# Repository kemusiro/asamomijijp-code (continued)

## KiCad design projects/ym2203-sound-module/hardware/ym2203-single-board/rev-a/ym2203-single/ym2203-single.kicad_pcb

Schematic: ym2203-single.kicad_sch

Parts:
A1: Raspberry Pi Pico 2; A1
A2: AE-PCM5102A / I2S 48kHz; A2
A3: AE-LLCNV-LVC8T245; A3
A4: AE-LLCNV-LVC8T245; A4
C1: 47u 10V; C1
C2: 10u 10V; C2
C3: 100n; C3
C4: 10u 10V; C4
C5: 100n; C5
C6: 100n; C6
C7: 100n; C7
C8: 100n; C8
C9: 100n; C9
C10: 100n; C10
C11: 100n; C11
C12: 100n; C12
C13: 2.2u X7R 10V; C13
C14: 2.2u X7R 10V; C14
C15: 1u X7R 10V; C15
C16: 100n; C16
C17: 100n; C17
C18: 100n; C18
C19: 10u 10V; C19
C20: 10u 10V; C20
C21: 10u 10V; C21
C22: 2.2n C0G; C22
C23: 100n; C23
C24: 10u 10V; C24
C25: 4.7u BP 10V; C25
C26: 4.7u BP 10V; C26
C27: 4.7u BP 10V; C27
C28: 4.7u BP 10V; C28
C29: 47p; C29
C30: 100n; C30
C31: 4.7u BP 10V; C31
D1: SS14 / A=+5V K=VSYS; D1
F1: PTC 0.5A hold; F1
H1: M3 / 3.2mm NPTH; H1
H2: M3 / 3.2mm NPTH; H2
H3: M3 / 3.2mm NPTH; H3
H4: M3 / 3.2mm NPTH; H4
JHOST: HOST 3.3V I2C; JHOST
JLINE: TRS JACK / AMS-22 LINE IN; JLINE
JPOWER: MAIN INPUT / REGULATED DC 5V; JPOWER
JRUN: RESET SWITCH; JRUN
JVOL: EXTERNAL SINGLE 10k A POT; JVOL
Q1: MMBT3904 / B1 E2 C3; Q1
R1: 4.7k; R1
R2: 4.7k; R2
R3: 4.7k; R3
R4: 10k; R4
R5: 10k; R5
R6: 10k; R6
R7: 47; R7
R8: 47; R8
R9: 47; R9
R10: 47; R10
R11: 47; R11
R12: 470; R12
R13: 10k 1%; R13
R14: 10k 1%; R14
R15: 100k 1%; R15
R16: 100k 1%; R16
R17: 100k 1%; R17
R18: 100k 1%; R18
R19: 22k 1%; R19
R20: 10k; R20
R21: 100k; R21
R22: 10k; R22
R23: 100k; R23
R24: 100; R24
R25: 100; R25
RN1: RKC8BD103J; RN1
RN2: RKC8BD103J; RN2
RN3: RKC4BD103J; RN3
RN4: RKC4BD103J; RN4
RN5: RKC8BD102J; RN5
RN6: RKC8BD103J; RN6
TP1: +5V; TP1
TP2: +3V3; TP2
TP3: GND; TP3
TP4: ARM; TP4
TP5: RESET_N; TP5
TP6: Y_SD; TP6
TP7: Y_CLK; TP7
TP8: Y_SH; TP8
TP9: CLK4; TP9
TP10: MIX_MONO; TP10
TP11: VREF; TP11
TP12: DAC_L; TP12
U1: YM2203C / DIP40; U1
U2: 74LCX245FT / 3.3V; U2
U3: 74LCX245FT / 3.3V; U3
U4: TC74HC04AP / 3.3V; U4
U5: TC74HC00AP / 3.3V; U5
U6: TC74HC32AP / 3.3V; U6
U7: TC74HC74AP / 5V; U7
U8: MCP6022-I/P / reference + mono mixer; U8
U9: CD74HC4053E / line mute; U9
U10: TC74HC08AP / 3.3V; U10
X1: 8MHz 5V oscillator; X1

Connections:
/+3V3: A1.36 (3V3 OUT), A2.1 (CPVDD), A2.8 (AVDD), A2.20 (DVDD), A3.1 (VA), A3.3 (DIR A>B), A3.24 (VA), A4.1 (VA), A4.3 (DIR A>B), A4.24 (VA), C2.1, C5.1, C6.1, C7.1, C8.1, C9.1, C10.1, C16.1, C17.1, C18.1, C19.1, C20.1, C21.1, R1.2, R2.2, R4.2, R5.2, RN3.1 (COM), TP2.1, U2.1 (DIR A>B), U2.20 (VCC), U3.1 (DIR A>B), U3.20 (VCC), U4.14 (VCC), U5.14 (VCC), U6.14 (VCC), U10.14 (VCC)
/+5V: A3.23 (VB), A4.23 (VB), C1.1, C3.1, C4.1, C11.1, C12.1, C23.1, C30.1, D1.2 (A), F1.2, R13.1, R22.1, RN4.1 (COM), TP1.1, U1.21 (VDD), U7.1 (CLR1_N), U7.4 (PRE1_N), U7.10 (PRE2_N), U7.13 (CLR2_N), U7.14 (VCC), U8.8 (VDD), U9.16 (VCC), X1.8 (VCC)
/A0: A1.11 (GP8 / A0), A4.4 (A1), RN2.3 (R2)
/ARM: A1.29 (GP22 / ARM), RN2.2 (R1), TP4.1, U4.1 (1A), U5.1 (1A), U5.4 (2A), U10.1 (1A), U10.4 (2A), U10.9 (3A)
/CAPM: A2.4 (CAPM), C13.2
/CAPP: A2.2 (CAPP), C13.1
/CLK4: R8.2, TP9.1, U1.38 (PHI_M 4MHz)
/CLK8: R7.2, U7.3 (CLK1)
/CLK_FB: U7.2 (D1), U7.6 (Q1_N)
/CS_N: A1.17 (GP13 / CS_N), RN3.2 (R1), U6.1 (CS_N)
/D0: A1.1 (GP0 / D0), A3.4 (A1), RN1.2 (R1), U2.18 (B1)
/D1: A1.2 (GP1 / D1), A3.5 (A2), RN1.3 (R2), U2.17 (B2)
/D2: A1.4 (GP2 / D2), A3.6 (A3), RN1.4 (R3), U2.16 (B3)
/D3: A1.5 (GP3 / D3), A3.7 (A4), RN1.5 (R4), U2.15 (B4)
/D4: A1.6 (GP4 / D4), A3.8 (A5), RN1.6 (R5), U2.14 (B5)
/D5: A1.7 (GP5 / D5), A3.9 (A6), RN1.7 (R6), U2.13 (B6)
/D6: A1.9 (GP6 / D6), A3.10 (A7), RN1.8 (R7), U2.12 (B7)
/D7: A1.10 (GP7 / D7), A3.11 (A8), RN1.9 (R8), U2.11 (B8)
/DAC_ALLOW: A1.31 (GP26 / DAC_ALLOW), RN2.5 (R4), U10.5 (2B)
/DAC_BCK: A2.13 (BCK), R10.2
/DAC_DIN: A2.14 (DIN), R9.2
/DAC_L: A2.6 (OUTL), R12.1, TP12.1
/DAC_LRCK: A2.15 (LRCK), R11.2
/DAC_XSMT: A2.17 (XSMT), R6.1, U10.6 (2Y)
/DIV4: R8.1, U7.5 (Q1)
/EXT_5V: F1.1, JPOWER.1 (EXT_5V)
/FM_CLK: A1.22 (GP17 / FM_CLK), RN2.8 (R7), U3.17 (B2)
/FM_FILTER: C22.1, C28.1, R12.2
/FM_FILTER_AC: C28.2, R18.1
/FM_SD: A1.21 (GP16 / FM_SD), RN2.7 (R6), U3.18 (B1)
/FM_SH: A1.24 (GP18 / FM_SH), RN2.9 (R8), U3.16 (B3)
/GND: A1.3 (GND), A1.8 (GND), A1.13 (GND), A1.18 (GND), A1.23 (GND), A1.28 (GND), A1.33 (GND), A1.38 (GND), A2.3 (CPGND), A2.9 (AGND), A2.10 (DEMP), A2.11 (FLT), A2.12 (SCK), A2.16 (FMT), A2.19 (DGND), A3.12 (GND), A3.13 (GND), A3.22 (GND), A4.2 (OE_N), A4.9 (A6), A4.10 (A7), A4.11 (A8), A4.12 (GND), A4.13 (GND), A4.22 (GND), C1.2, C2.2, C3.2, C4.2, C5.2, C6.2, C7.2, C8.2, C9.2, C10.2, C11.2, C12.2, C14.2, C15.2, C16.2, C17.2, C18.2, C19.2, C20.2, C21.2, C22.2, C23.2, C24.2, C30.2, JHOST.1 (GND), JHOST.4 (GND), JLINE.3 (GND), JPOWER.2 (GND), JRUN.2 (GND), JVOL.3 (GND), Q1.2 (E), R3.2, R6.2, R14.2, R21.2, R23.2, RN1.1 (COM), RN2.1 (COM), RN5.1 (COM), RN6.1 (COM), TP3.1, U1.1 (GND), U1.17 (GND), U2.10 (GND), U3.6 (A5), U3.7 (A6), U3.8 (A7), U3.9 (A8), U3.10 (GND), U3.19 (OE_N), U4.5 (3A), U4.7 (GND), U4.9 (4A), U4.11 (5A), U4.13 (6A), U5.7 (GND), U5.9 (3A), U5.10 (3B), U5.12 (4A), U5.13 (4B), U6.7 (GND), U6.12 (4A), U6.13 (4B), U7.7 (GND), U7.11 (CLK2), U7.12 (D2), U8.4 (VSS), U9.1 (Y1), U9.2 (Y0), U9.3 (Z1), U9.5 (Z0), U9.6 (INH), U9.7 (VEE), U9.8 (GND), U9.9 (C), U9.10 (B), U10.7 (GND), U10.12 (4A), U10.13 (4B), X1.4 (GND)
/HOST_SCL: A1.27 (GP21 / HOST_SCL), JHOST.3 (HOST_SCL), R2.1
/HOST_SDA: A1.26 (GP20 / HOST_SDA), JHOST.2 (HOST_SDA), R1.1
/I2S_BCLK: A1.15 (GP11 / I2S_BCLK), R10.1
/I2S_DATA: A1.14 (GP10 / I2S_DATA), R9.1
/I2S_LRCK: A1.16 (GP12 / I2S_LRCK), R11.1
/IRQ_N: A1.34 (GP28 / IRQ_N), RN3.5 (R4), U3.15 (B4)
/LDOO: A2.18 (LDOO), C15.1
/LINE_ALLOW: A1.25 (GP19 / LINE_ALLOW), RN2.6 (R5), U10.10 (3B)
/LINE_L: JLINE.1 (LINE_L), R24.2
/LINE_R: JLINE.2 (LINE_R), R25.2
/LINE_RUN: R20.1, U10.8 (3Y)
/MIX_MONO: C29.1, R19.1, TP10.1, U8.7 (OUTB), U9.12 (X0)
/MUTED_MONO: C31.1, U9.14 (X)
/MUTE_5V: Q1.3 (C), R22.2, U9.11 (A)
/MUTE_BASE: Q1.1 (B), R20.2, R21.1
/NOT_ARM: U4.2 (1Y), U6.2 (NOT_ARM), U6.5 (NOT_ARM), U6.10 (NOT_ARM)
/NOT_RD_N: U4.4 (2Y), U5.5 (2B)
/OE_READ_N: R5.1, U2.19 (OE_N), U5.6 (2Y)
/OE_WRITE_N: A3.2 (OE_N), U5.3 (1Y)
/OSC8: R7.1, X1.5 (OUT)
/OUT_AC: C31.2, JVOL.1 (OUT_AC), R23.1
/PICO_RUN: A1.30 (RUN), JRUN.1 (PICO_RUN)
/RD_N: A1.20 (GP15 / RD_N), RN3.4 (R3), U4.3 (2A), U5.2 (1B), U6.9 (RD_N)
/REF_RAW: C24.1, R13.2, R14.1, U8.3 (INA+)
/RESET_N: A4.5 (A2), TP5.1, U10.3 (1Y)
/RESET_RELEASE: A1.12 (GP9 / RESET_RELEASE), RN2.4 (R3), U10.2 (1B)
/SAFE_CS_N: A4.6 (A3), U6.3 (SAFE_CS_N)
/SAFE_RD_N: A4.8 (A5), U6.8 (SAFE_RD_N)
/SAFE_WR_N: A4.7 (A4), U6.6 (SAFE_WR_N)
/SSG_A: C25.1, RN5.2 (R1), U1.20 (SSG_A)
/SSG_A_AC: C25.2, R15.1
/SSG_B: C26.1, RN5.3 (R2), U1.19 (SSG_B)
/SSG_B_AC: C26.2, R16.1
/SSG_C: C27.1, RN5.4 (R3), U1.18 (SSG_C)
/SSG_C_AC: C27.2, R17.1
/SUM_MONO: C29.2, R15.2, R16.2, R17.2, R18.2, R19.2, U8.6 (INB-)
/VNEG: A2.5 (VNEG), C14.1
/VOL_MONO: JVOL.2 (VOL_MONO), R24.1, R25.1
/VREF: TP11.1, U8.1 (OUTA), U8.2 (INA-), U8.5 (INB+), U9.13 (X1)
/VSYS: A1.39 (VSYS), D1.1 (K)
/WR_N: A1.19 (GP14 / WR_N), RN3.3 (R2), U6.4 (WR_N)
/Y_A0: A4.21 (B1), U1.37 (A0)
/Y_CLK: TP7.1, U1.39 (CLK), U3.3 (A2)
/Y_CS_N: A4.19 (B3), RN4.2 (R1), U1.34 (CS_N)
/Y_D0: A3.21 (B1), RN6.2 (R1), U1.40 (D0), U2.2 (A1)
/Y_D1: A3.20 (B2), RN6.3 (R2), U1.2 (D1), U2.3 (A2)
/Y_D2: A3.19 (B3), RN6.4 (R3), U1.3 (D2), U2.4 (A3)
/Y_D3: A3.18 (B4), RN6.5 (R4), U1.4 (D3), U2.5 (A4)
/Y_D4: A3.17 (B5), RN6.6 (R5), U1.5 (D4), U2.6 (A5)
/Y_D5: A3.16 (B6), RN6.7 (R6), U1.6 (D5), U2.7 (A6)
/Y_D6: A3.15 (B7), RN6.8 (R7), U1.7 (D6), U2.8 (A7)
/Y_D7: A3.14 (B8), RN6.9 (R8), U1.8 (D7), U2.9 (A8)
/Y_IRQ: R4.1, U1.25 (IRQ_N), U3.5 (A4)
/Y_RD_N: A4.17 (B5), RN4.4 (R3), U1.36 (RD_N)
/Y_RESET_N: A4.20 (B2), R3.1, U1.24 (RESET_N)
/Y_SD: TP6.1, U1.23 (SD), U3.2 (A1)
/Y_SH: TP8.1, U1.22 (SH), U3.4 (A3)
/Y_WR_N: A4.18 (B4), RN4.3 (R2), U1.35 (WR_N)

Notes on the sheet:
YM2203C SINGLE BOARD / Pico 2 / I2C + USB-MIDI / MONO LINE OUT
Rev A / GPIO approved 2026-10-18 / Prototype - hardware untested / See README before manufacture
Labels of the same name are connected. Pin numbers are physical pins. Mono mix duplicated to L/R line output for AMS-22. USB-MIDI requires firmware.
CONTROLLER / IO
YM / CLOCK
BUS / FM
SAFETY / POWER
DAC
ANALOG / PULLS / DECOUPLING / TEST

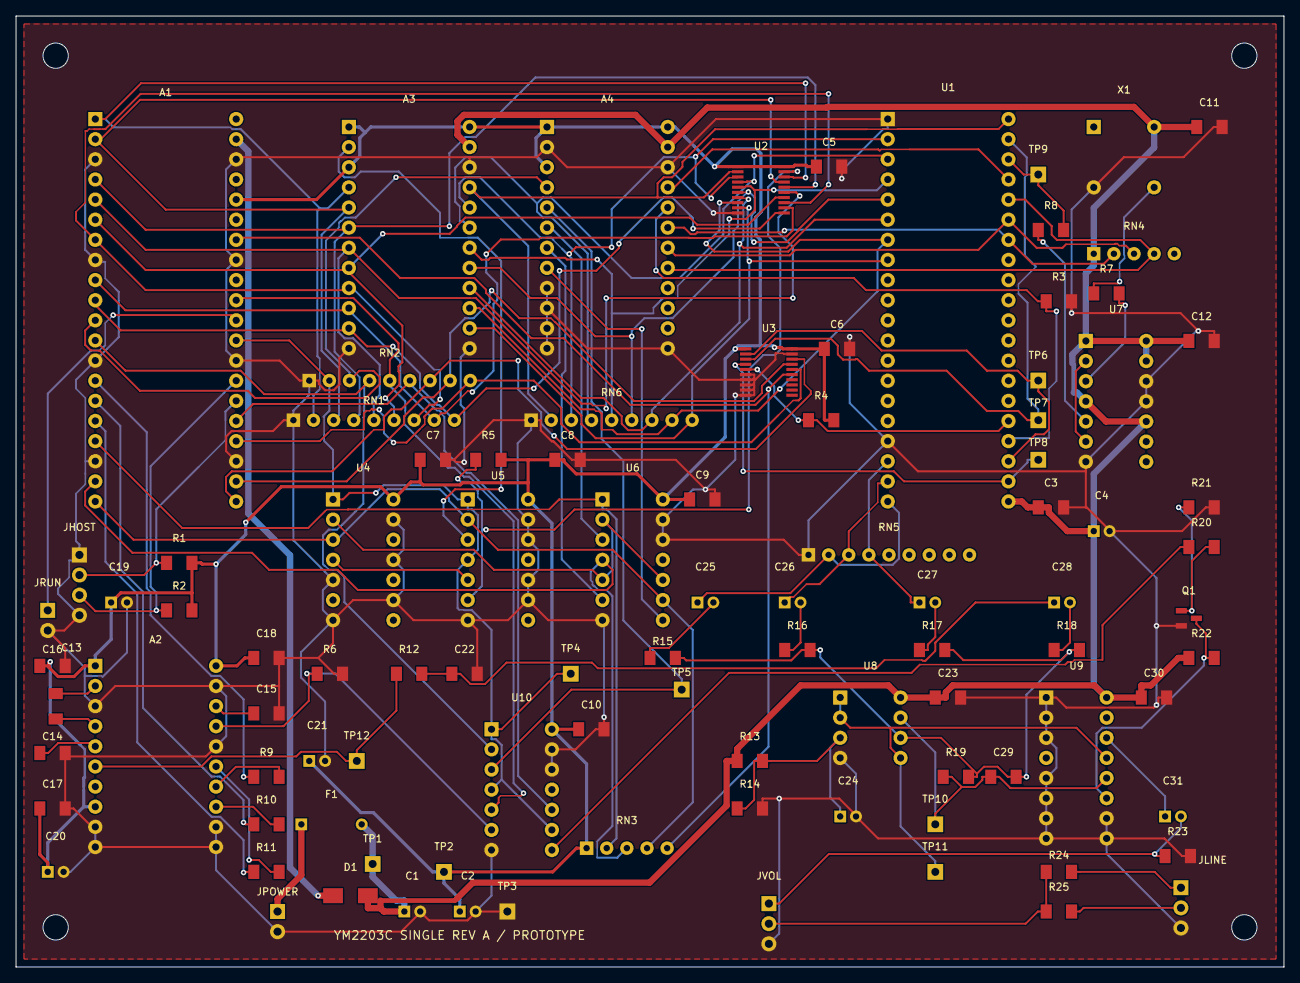
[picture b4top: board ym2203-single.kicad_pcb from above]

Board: 2 copper layers, 160.0 x 120.0 mm, 101 parts (0 on the bottom side), 90 nets.

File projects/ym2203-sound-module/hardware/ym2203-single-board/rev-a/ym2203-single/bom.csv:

reference,value,footprint,x_mm,y_mm,source,role
A1,Raspberry Pi Pico 2,SOUNDPCB:A1,10.0,13.0,https://datasheets.raspberrypi.com/pico/pico-2-datasheet.pdf,USB-MIDI uses the onboard USB connector; requires C/C++ firmware.
JHOST,HOST 3.3V I2C,SOUNDPCB:JHOST,8.0,68.0,,1=GND 2=SDA 3=SCL 4=GND. Host supply not connected.
JRUN,RESET SWITCH,SOUNDPCB:JRUN,4.0,75.0,,
JPOWER,MAIN INPUT / REGULATED DC 5V,SOUNDPCB:JPOWER,33.0,113.0,,1=regulated +5V 2=GND. External 5V required; no reverse-polarity or overvoltage protection.
F1,PTC 0.5A hold,SOUNDPCB:F1,36.0,102.0,,
D1,SS14 / A=+5V K=VSYS,SOUNDPCB:D1,40.0,111.0,,Blocks USB-to-main-supply backfeed through VSYS.
C1,47u 10V,SOUNDPCB:C1,49.0,113.0,,
C2,10u 10V,SOUNDPCB:C2,56.0,113.0,,
R1,4.7k,SOUNDPCB:R1,19.0,69.0,,Omit if host provides the bus pullup.
R2,4.7k,SOUNDPCB:R2,19.0,75.0,,Omit if host provides the bus pullup.
U1,YM2203C / DIP40,SOUNDPCB:U1,110.0,13.0,https://www.bitsavers.org/components/yamaha/YM2203_198911.pdf,
C3,100n,SOUNDPCB:C3,129.0,62.0,,Place immediately beside supply pin
C4,10u 10V,SOUNDPCB:C4,136.0,65.0,,
A3,AE-LLCNV-LVC8T245,SOUNDPCB:A3,42.0,14.0,https://akizukidenshi.com/catalog/g/g115778/,
A4,AE-LLCNV-LVC8T245,SOUNDPCB:A4,67.0,14.0,https://akizukidenshi.com/catalog/g/g115778/,
U2,74LCX245FT / 3.3V,SOUNDPCB:U2,94.0,19.0,https://akizukidenshi.com/goodsaffix/74LCX245FT_datasheet_ja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,
C5,100n,SOUNDPCB:C5,101.0,19.0,,Place immediately beside supply pin
U3,74LCX245FT / 3.3V,SOUNDPCB:U3,95.0,42.0,https://akizukidenshi.com/goodsaffix/74LCX245FT_datasheet_ja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,
C6,100n,SOUNDPCB:C6,102.0,42.0,,Place immediately beside supply pin
U4,TC74HC04AP / 3.3V,SOUNDPCB:U4,40.0,61.0,https://akizukidenshi.com/catalog/g/g114058/,
U5,TC74HC00AP / 3.3V,SOUNDPCB:U5,57.0,61.0,https://akizukidenshi.com/catalog/g/g110856/,
U6,TC74HC32AP / 3.3V,SOUNDPCB:U6,74.0,61.0,https://akizukidenshi.com/catalog/g/g112877/,
U10,TC74HC08AP / 3.3V,SOUNDPCB:U10,60.0,90.0,https://akizukidenshi.com/catalog/g/g114059/,
C7,100n,SOUNDPCB:C7,51.0,56.0,,Place immediately beside supply pin
C8,100n,SOUNDPCB:C8,68.0,56.0,,Place immediately beside supply pin
C9,100n,SOUNDPCB:C9,85.0,61.0,,Place immediately beside supply pin
C10,100n,SOUNDPCB:C10,71.0,90.0,,Place immediately beside supply pin
RN1,RKC8BD103J,SOUNDPCB:RN1,35.0,51.0,https://akizukidenshi.com/catalog/g/g111910/,
RN2,RKC8BD103J,SOUNDPCB:RN2,37.0,46.0,https://akizukidenshi.com/catalog/g/g111910/,
RN3,RKC4BD103J,SOUNDPCB:RN3,72.0,105.0,https://akizukidenshi.com/catalog/g/g111909/,
RN4,RKC4BD103J,SOUNDPCB:RN4,136.0,30.0,https://akizukidenshi.com/catalog/g/g111909/,
RN6,RKC8BD103J,SOUNDPCB:RN6,65.0,51.0,https://akizukidenshi.com/catalog/g/g111910/,
R3,4.7k,SOUNDPCB:R3,130.0,36.0,,
R4,10k,SOUNDPCB:R4,100.0,51.0,,
R5,10k,SOUNDPCB:R5,58.0,56.0,,
R6,10k,SOUNDPCB:R6,38.0,83.0,,
X1,8MHz 5V oscillator,SOUNDPCB:X1,136.0,14.0,https://akizukidenshi.com/goodsaffix/osc.pdf,
C11,100n,SOUNDPCB:C11,149.0,14.0,,Place immediately beside supply pin
R7,47,SOUNDPCB:R7,136.0,35.0,,
U7,TC74HC74AP / 5V,SOUNDPCB:U7,135.0,41.0,https://akizukidenshi.com/goodsaffix/TC74HC74AP_datasheet_ja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,
C12,100n,SOUNDPCB:C12,148.0,41.0,,Place immediately beside supply pin
R8,47,SOUNDPCB:R8,129.0,27.0,,
A2,AE-PCM5102A / I2S 48kHz,SOUNDPCB:A2,10.0,82.0,https://akizukidenshi.com/catalog/g/g111836/,OUTL used; OUTR intentionally unconnected. Not AE-DAC5102.
R9,47,SOUNDPCB:R9,30.0,96.0,,
R10,47,SOUNDPCB:R10,30.0,102.0,,
R11,47,SOUNDPCB:R11,30.0,108.0,,
C13,2.2u X7R 10V,SOUNDPCB:C13,5.0,85.5,,
C14,2.2u X7R 10V,SOUNDPCB:C14,3.0,93.0,,
C15,1u X7R 10V,SOUNDPCB:C15,30.0,88.0,,
C16,100n,SOUNDPCB:C16,3.0,82.0,,Place immediately beside supply pin
C17,100n,SOUNDPCB:C17,3.0,100.0,,Place immediately beside supply pin
C18,100n,SOUNDPCB:C18,30.0,81.0,,Place immediately beside supply pin
C19,10u 10V,SOUNDPCB:C19,12.0,74.0,,
C20,10u 10V,SOUNDPCB:C20,4.0,108.0,,
C21,10u 10V,SOUNDPCB:C21,37.0,94.0,,
R12,470,SOUNDPCB:R12,48.0,83.0,,
C22,2.2n C0G,SOUNDPCB:C22,55.0,83.0,,
U8,MCP6022-I/P / reference + mono mixer,SOUNDPCB:U8,104.0,86.0,https://akizukidenshi.com/goodsaffix/MCP6022.pdf,
C23,100n,SOUNDPCB:C23,116.0,86.0,,Place immediately beside supply pin
R13,10k 1%,SOUNDPCB:R13,91.0,94.0,,
R14,10k 1%,SOUNDPCB:R14,91.0,100.0,,
C24,10u 10V,SOUNDPCB:C24,104.0,101.0,,
C25,4.7u BP 10V,SOUNDPCB:C25,86.0,74.0,,
R15,100k 1%,SOUNDPCB:R15,80.0,81.0,,
C26,4.7u BP 10V,SOUNDPCB:C26,97.0,74.0,,
R16,100k 1%,SOUNDPCB:R16,97.0,80.0,,
C27,4.7u BP 10V,SOUNDPCB:C27,114.0,74.0,,
R17,100k 1%,SOUNDPCB:R17,114.0,80.0,,
C28,4.7u BP 10V,SOUNDPCB:C28,131.0,74.0,,
R18,100k 1%,SOUNDPCB:R18,131.0,80.0,,
RN5,RKC8BD102J,SOUNDPCB:RN5,100.0,68.0,https://akizukidenshi.com/catalog/g/g113722/,
R19,22k 1%,SOUNDPCB:R19,117.0,96.0,,
C29,47p,SOUNDPCB:C29,123.0,96.0,,
U9,CD74HC4053E / line mute,SOUNDPCB:U9,130.0,86.0,https://akizukidenshi.com/catalog/g/g113266/,
C30,100n,SOUNDPCB:C30,142.0,86.0,,Place immediately beside supply pin
Q1,MMBT3904 / B1 E2 C3,SOUNDPCB:Q1,148.0,76.0,https://www.onsemi.com/pdf/datasheet/mmbt3904lt1-d.pdf,
R20,10k,SOUNDPCB:R20,148.0,67.0,,
R21,100k,SOUNDPCB:R21,148.0,62.0,,
R22,10k,SOUNDPCB:R22,148.0,81.0,,
C31,4.7u BP 10V,SOUNDPCB:C31,145.0,101.0,,
R23,100k,SOUNDPCB:R23,145.0,106.0,,
JVOL,EXTERNAL SINGLE 10k A POT,SOUNDPCB:JVOL,95.0,112.0,,1=HIGH 2=WIPER 3=LOW(GND). Mono level; independent of mute.
R24,100,SOUNDPCB:R24,130.0,108.0,,
R25,100,SOUNDPCB:R25,130.0,113.0,,
JLINE,TRS JACK / AMS-22 LINE IN,SOUNDPCB:JLINE,147.0,110.0,,1=TIP 2=RING 3=SLEEVE. Identical mono L/R through separate 100-ohm resistors. No power amplifier.
TP1,+5V,SOUNDPCB:TP1,45.0,107.0,,
TP2,+3V3,SOUNDPCB:TP2,54.0,108.0,,
TP3,GND,SOUNDPCB:TP3,62.0,113.0,,
TP4,ARM,SOUNDPCB:TP4,70.0,83.0,,
TP5,RESET_N,SOUNDPCB:TP5,84.0,85.0,,
TP6,Y_SD,SOUNDPCB:TP6,129.0,46.0,,
TP7,Y_CLK,SOUNDPCB:TP7,129.0,51.0,,
TP8,Y_SH,SOUNDPCB:TP8,129.0,56.0,,
TP9,CLK4,SOUNDPCB:TP9,129.0,20.0,,
TP10,MIX_MONO,SOUNDPCB:TP10,116.0,102.0,,
TP11,VREF,SOUNDPCB:TP11,116.0,108.0,,
TP12,DAC_L,SOUNDPCB:TP12,43.0,94.0,,
H1,M3 / 3.2mm NPTH,SOUNDPCB:H1,5.0,5.0,,
H2,M3 / 3.2mm NPTH,SOUNDPCB:H2,155.0,5.0,,
H3,M3 / 3.2mm NPTH,SOUNDPCB:H3,5.0,115.0,,
H4,M3 / 3.2mm NPTH,SOUNDPCB:H4,155.0,115.0,,
